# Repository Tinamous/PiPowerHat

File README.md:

Raspberry Pi Power Hat
======================

WORK IN PROGRESS - Not tested!

A Hat for the Raspberry Pi to supply 5V though the 40pin header from a 7-36V DC source rather than using the USB plug.

When using the 7" Pi Display the voltage drop across the USB cable (esp. if long) may be too much for the Pi. This hat allows a higher voltage to be dropped 
right as it is needed and distributed to the Pi and the display so reducing the voltage drop.

Rather than design and source a buck switching supply this hat uses one of the many cheap "eBay" buck converts that have the 
standard 7805 footprint (Don't use an actual 7805!).

e.g. a PM-5033-1 36 V In, 5V 2.5A Out buck converter. http://www.ebay.co.uk/itm/262241859833

The PCB also includes:
* INA219 to measure the power via a current sense resistor (R4 - value to be determined)
* The normal Pi HAT EEprom
* DS18B20 - SOIC 8 footprint by the converter to monitor PCB temperature.
* DS18B20 - TO-92 (3 Pin) to measure ambient temperature
* 3 Pin Molex header for off-board DB18B20's
* 4 Pin Molex header for Pi 7" display (GND, 5V, I2C connections).

Pi Hat original schema/PCB (connector, shape, EEprom) but Ivan Zilic (http://www.flyfish-tech.com)
Source: 
https://www.raspberrypi.org/forums/viewtopic.php?f=100&t=82618
http://www.flyfish-tech.com/pub/RasPi-BplusHAT.zip

Component Libraries:
SparkFun - https://github.com/sparkfun/SparkFun-Eagle-Libraries
DS18B20-SOIC - ??
INA219 - Farnell

See https://github.com/Tinamous/OctoPrint-PiPower for an OctoPrint plugin to monitor and control.

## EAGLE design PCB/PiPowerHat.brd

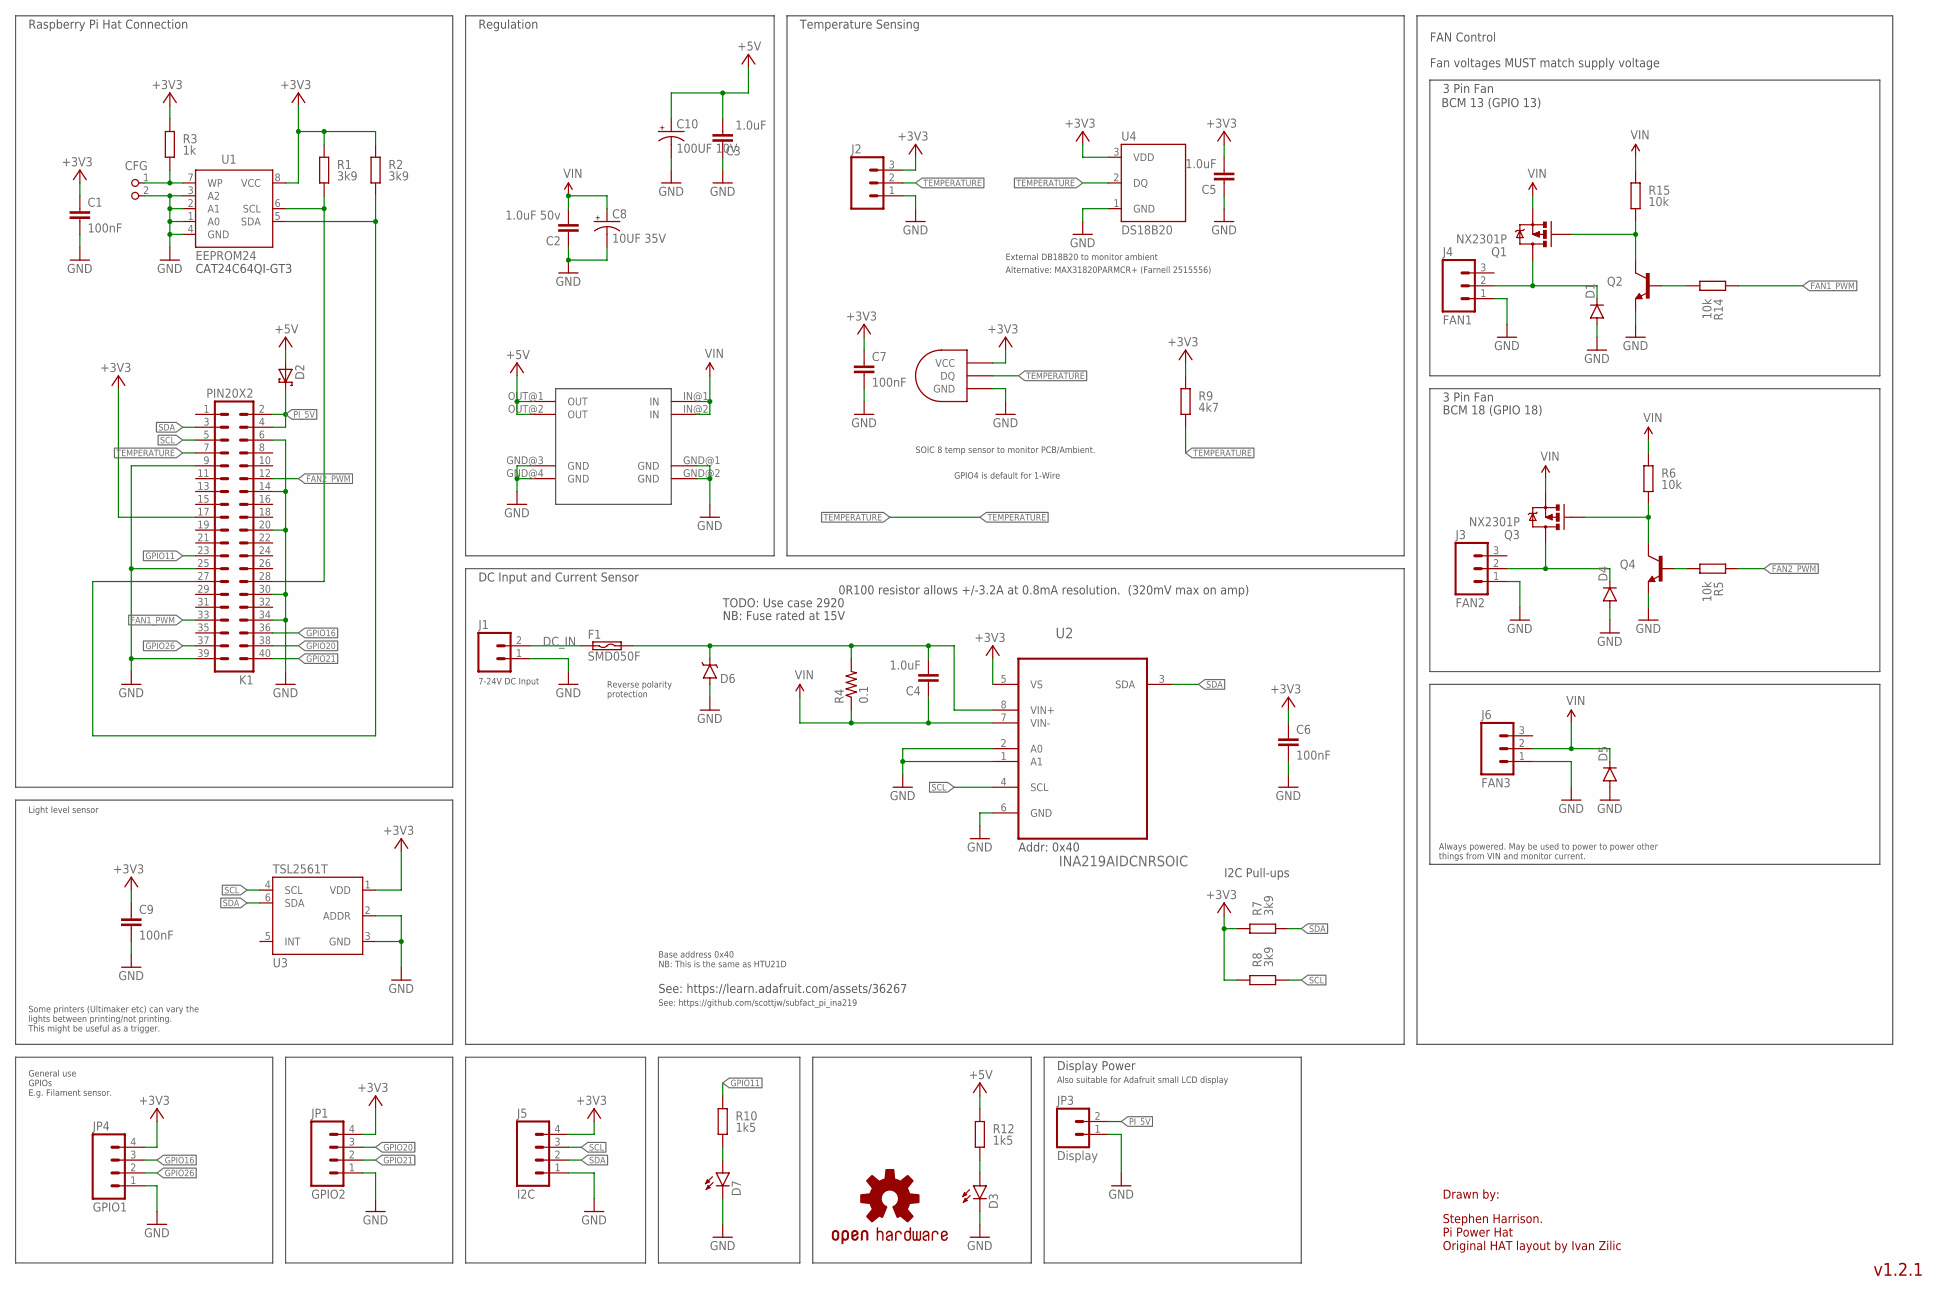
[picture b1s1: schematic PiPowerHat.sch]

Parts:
C1, C6, C7, C9: 100nF; C0805K
C2: 1.0uF 50v; 0805-CAP
C3, C4, C5: 1.0uF; 0805-CAP
C8: 10UF 35V; EIA6032-NOM; FARNELL 197634
C10: 100UF 10V; EIA6032-NOM
CFG: PIN2_100; PIN_W_2
D1, D4, D5: DIODESOD123; SOD-123
D2: MBRS340T3G; SMC; FARNELL 9557377
D3: LED1206-BOTTOM; LED-1206-BOTTOM
D6: B340A; SMA-DIODE
D7: LED1206; LED-1206
F1: SMD050F; FARNELL 1822231
J1: M025MM; SCREWTERMINAL-5MM-2
J2: M03POLAR; MOLEX-1X3
J3: FAN2; MOLEX-1X3
J4: FAN1; MOLEX-1X3
J5: I2C; MOLEX-1X4
J6: FAN3; MOLEX-1X3
JP1: GPIO2; MOLEX-1X4
JP3: Display; MOLEX-1X2
JP4: GPIO1; MOLEX-1X4
K1: PIN20X2; PIN_20X2
LOGO1: OSHW-LOGOM; OSHW-LOGO-M
Q1, Q3: NX2301P; SOT23-3
Q2, Q4: TRANSISTOR_NPNSOT23-3; SOT23-3
R1, R2, R7, R8: 3k9; M0805; TOLERANCE 5%
R3: 1k; M0805; TOLERANCE 5%
R4: 0.1; 2512
R5, R6, R14, R15: 10k; M0805; TOLERANCE 5%
R9: 4k7; M0805; TOLERANCE 5%
R10, R12: 1k5; M0805; TOLERANCE 5%
RG1: MINI-BUCK-MODULE-3A
U1: EEPROM24; SOIC8; FARNELL 2463718
U2: INA219AIDCNRSOIC; SO08
U3: TSL2561T; TMB-6
U4: DS18B20; TO-92-AMMO
U5: DS1820SOIC; DS18B20_SOIC

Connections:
+3V3: C1.1, C5.2, C6.1, C7.1, C9.1, J2.3, J5.4, JP1.4, JP4.4, K1.17, R1.2, R2.2, R3.2, R7.2, R8.2, R9.2, U1.8 (VCC), U2.5 (VS), U3.1 (VDD), U4.3 (VDD), U5.VCC
+5V: C3.2, C10.A (+), D2.A, R12.2, RG1.OUT@1 (OUT), RG1.OUT@2 (OUT)
DC_IN: F1.1, J1.2
FAN1_PWM: K1.33, R14.2
FAN2_PWM: K1.12, R5.2
GND: C1.2, C2.1, C3.1, C5.1, C6.2, C7.2, C8.C (-), C9.2, C10.C (-), CFG.2, D1.A, D3.C, D4.A, D5.A, D6.A, D7.C, J1.1, J2.1, J3.1, J4.1, J5.1, J6.1, JP1.1, JP3.1, JP4.1, K1.6, K1.9, K1.14, K1.20, K1.25, K1.30, K1.34, K1.39, Q2.2 (E), Q4.2 (E), RG1.GND@1 (GND), RG1.GND@2 (GND), RG1.GND@3 (GND), RG1.GND@4 (GND), U1.1 (A0), U1.2 (A1), U1.3 (A2), U1.4 (GND), U2.1 (A1), U2.2 (A0), U2.6 (GND), U3.2 (ADDR), U3.3 (GND), U4.1 (GND), U5.GND
GPIO11: K1.23, R10.2
GPIO16: JP4.3, K1.36
GPIO20: JP1.3, K1.38
GPIO21: JP1.2, K1.40
GPIO26: JP4.2, K1.37
ID_SC: K1.28, R1.1, U1.6 (SCL)
ID_SD: K1.27, R2.1, U1.5 (SDA)
unnamed: D4.C, J3.2, Q3.3 (D)
unnamed: Q4.1 (B), R5.1
unnamed: CFG.1, R3.1, U1.7 (WP)
unnamed: D3.A, R12.1
unnamed: C4.2, D6.C, F1.2, R4.2, U2.8 (VIN+)
unnamed: Q3.1 (G), Q4.3 (C), R6.1
unnamed: D1.C, J4.2, Q1.3 (D)
unnamed: Q1.1 (G), Q2.3 (C), R15.1
unnamed: D7.A, R10.1
unnamed: Q2.1 (B), R14.1
PI_5V: D2.C, JP3.2, K1.2, K1.4
SCL: J5.3, K1.5, R8.1, U2.4 (SCL), U3.4 (SCL)
SDA: J5.2, K1.3, R7.1, U2.3 (SDA), U3.6 (SDA)
TEMPERATURE: J2.2, K1.7, R9.1, U4.2 (DQ), U5.DQ
VIN: C2.2, C4.1, C8.A (+), D5.C, J6.2, Q1.2 (S), Q3.2 (S), R4.1, R6.2, R15.2, RG1.IN@1 (IN), RG1.IN@2 (IN), U2.7 (VIN-)

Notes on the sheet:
Drawn by:
Stephen Harrison. Pi Power Hat Original HAT layout by Ivan Zilic
v1.2.1
SOIC 8 temp sensor to monitor PCB/Ambient.
External DB18B20 to monitor ambient
CAT24C64QI-GT3
I2C Pull-ups
Temperature Sensing
Regulation
Raspberry Pi Hat Connection
Display Power
DC Input and Current Sensor
See: https://learn.adafruit.com/assets/36267
0R100 resistor allows +/-3.2A at 0.8mA resolution. (320mV max on amp)
Addr: 0x40
TODO: Use case 2920
NB: Fuse rated at 15V
Reverse polarity protection
7-24V DC Input
Base address 0x40 NB: This is the same as HTU21D
See: https://github.com/scottjw/subfact_pi_ina219
GPIO4 is default for 1-Wire
FAN Control
3 Pin Fan
Fan voltages MUST match supply voltage
General use GPIOs E.g. Filament sensor.
Also suitable for Adafruit small LCD display
Light level sensor
Some printers (Ultimaker etc) can vary the lights between printing/not printing. This might be useful as a trigger.
BCM 18 (GPIO 18)
BCM 13 (GPIO 13)
Always powered. May be used to power to power other things from VIN and monitor current.
Alternative: MAX31820PARMCR+ (Farnell 2515556)

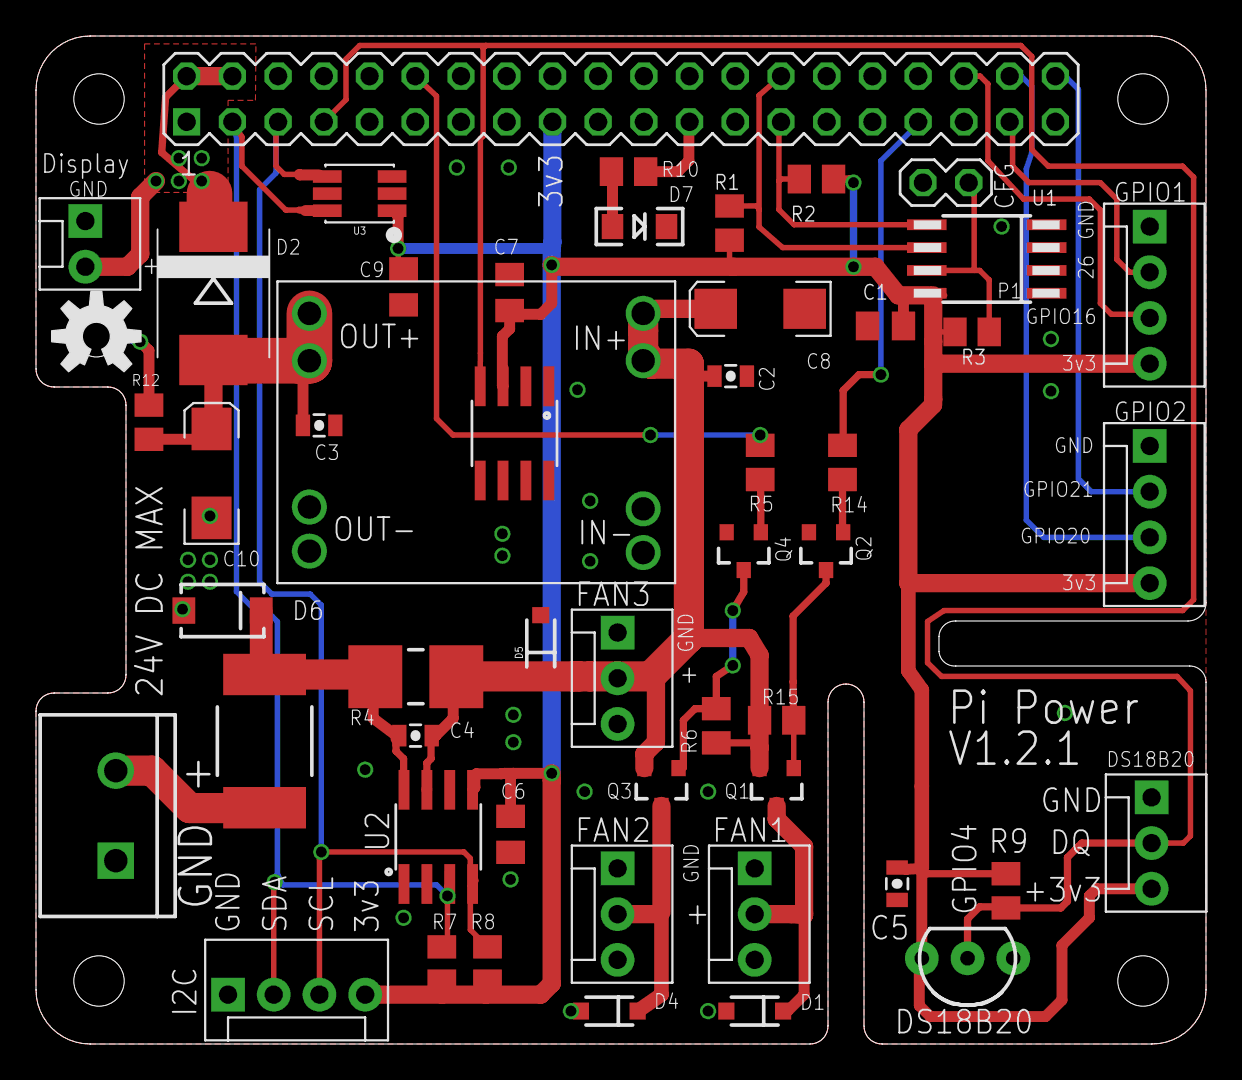
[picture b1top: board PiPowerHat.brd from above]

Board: 2 copper layers, 65.0 x 56.0 mm, 53 parts (1 on the bottom side), 28 nets.

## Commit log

2016-12-12 Initial version as sent to DirtyPCBs.
2016-12-12 Added gitignore
2016-12-12 Corrected dimension measurements to be on the measurements layer, not dimensions.
    Added Version and name/date.
    Printed schema and PCB to PDFs
    Added readme.
2016-12-22 Added notes for eeprom
2016-12-23 Tidied up schematic/board with feedback from 1st build.
    Added BOM.
2016-12-23 Update for PTC fuse size issue
2016-12-24 Improved routing to not use bottom layer so much
2016-12-25 Improved routing to increase ground plain, change IO pins used with option to select between 2 IO pins for temperature sensors.
    Added OSH logo and rear LED.
2017-02-27 Changed 7805 style regulator to the 3A buck regulator.
    Added DotStar LED strip connector (clk/data).
    Added 2 GPIO port + power connector.
    Added 2x fan connectors (1x 4 pin PWM, 1x 3 pin PWM power)
    Added fuse.
    Moved current/voltage sensor to pre-regulator to monitor the input voltage.
    Moved board temperature sensor to be under regulator module.
2017-03-07 Added link to Octoprint plugin
2017-05-17 Added some improvements...
2017-05-17 Added pin numbers for the fans
2017-05-20 Documentation improvements to V1.2 PCB
2017-07-22 Update to rearrange the board a bit better.
2017-07-31 Coped V1.2 to V1.2 folder so it's easier to have multiple versions available
2017-08-01 Removed 3v3/5V logic converter in favour of just a second 3v3 GPIO port.
    Added Fan3 which is permenantly connected to the VIn supply to allow it to be used to power a fan or something else whilst still having current monitoring without the current restriction of the p-cha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
    Slight improvements in routing.
2017-08-01 Flipped temperature sensor connector improved silk screen.
2017-08-01 Updated silk screen. Sent to DirtyPCBs.
2017-08-01 Copied V1.2.1 PCB/schematic to the 1.2.1 folder.
2017-08-21 Added Github link to the bottom of the board.
    Ordered ENIG batch from DirtyPCBs.

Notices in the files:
parts and their libraries:
SparkFun-Capacitors: Licensing: Creative Commons ShareAlike 4.0 International - https://creativecommons.org/licenses/by-sa/4.0
